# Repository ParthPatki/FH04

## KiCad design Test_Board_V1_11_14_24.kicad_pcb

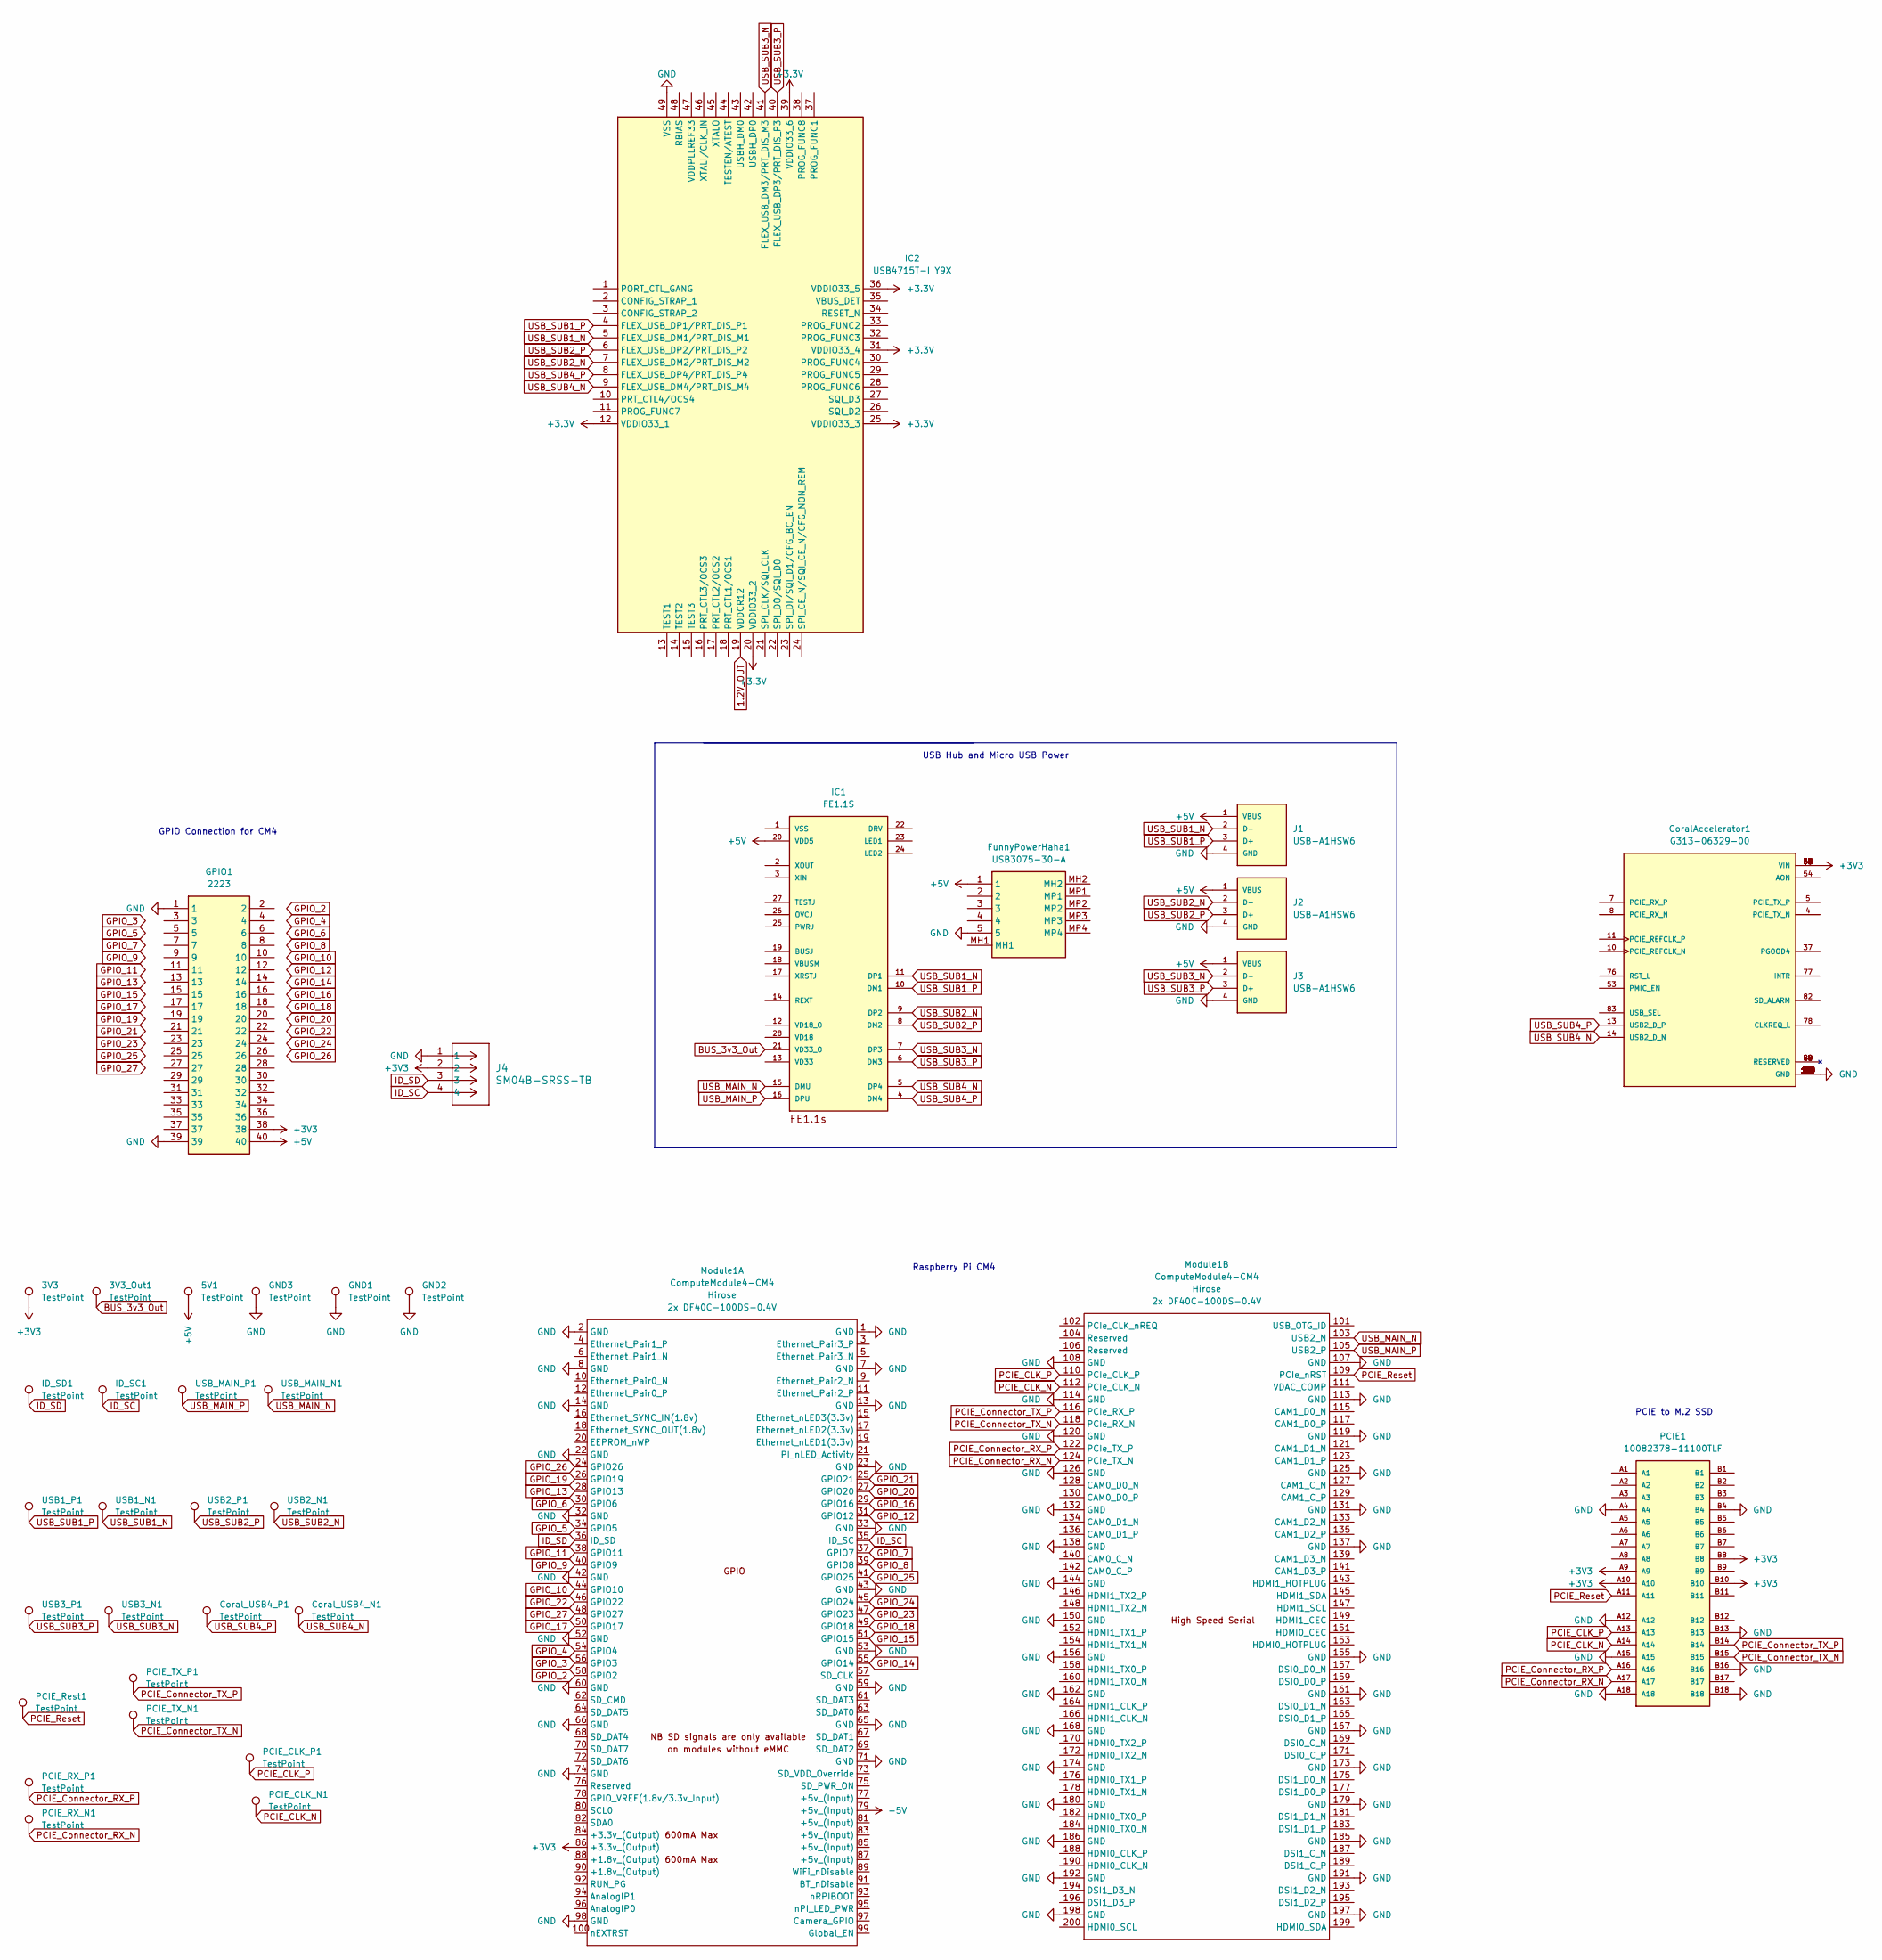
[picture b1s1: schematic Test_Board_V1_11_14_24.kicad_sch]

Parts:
3V3, 3V3_Out1, 5V1: TestPoint; TestPoint_Loop_D1.80mm_Drill1.0mm_Beaded
CoralAccelerator1: G313-06329-00; MODULE_G313-06329-00; PARTREV 1.3
Coral_USB4_N1, Coral_USB4_P1: TestPoint; TestPoint_Loop_D1.80mm_Drill1.0mm_Beaded
FunnyPowerHaha1: USB3075-30-A; USB307530A; Manufacturer_Part_Number USB3075-30-A
GND1, GND2, GND3: TestPoint; TestPoint_Loop_D1.80mm_Drill1.0mm_Beaded
GPIO1: 2223; RHDR40W64P254X254_2X20_5105X500X865P; Manufacturer_Part_Number 2223
IC1: FE1.1S; FE1.1S_SSOP-28
IC2: USB4715T-I_Y9X; QFN50P700X700X100-49N-D; Mouser Part Number 579-USB4715T-I/Y9X
ID_SC1: TestPoint; TestPoint_Loop_D1.80mm_Drill1.0mm_Beaded
ID_SD1: TestPoint; TestPoint_Loop_D1.80mm_Drill1.0mm_Beaded
J1, J2, J3: USB-A1HSW6; OST_USB-A1HSW6; PARTREV A
J4: SM04B-SRSS-TB; CONN_SM04B-SRSS-TB_JST
Module1: ComputeModule4-CM4; Raspberry-Pi-4-Compute-Module
PCIE1: 10082378-11100TLF; AMPHENOL_10018783-11110TLF; PARTREV H
PCIE_CLK_N1: TestPoint; TestPoint_Loop_D1.80mm_Drill1.0mm_Beaded
PCIE_CLK_P1: TestPoint; TestPoint_Loop_D1.80mm_Drill1.0mm_Beaded
PCIE_RX_N1: TestPoint; TestPoint_Loop_D1.80mm_Drill1.0mm_Beaded
PCIE_RX_P1: TestPoint; TestPoint_Loop_D1.80mm_Drill1.0mm_Beaded
PCIE_Rest1: TestPoint; TestPoint_Loop_D1.80mm_Drill1.0mm_Beaded
PCIE_TX_N1: TestPoint; TestPoint_Loop_D1.80mm_Drill1.0mm_Beaded
PCIE_TX_P1: TestPoint; TestPoint_Loop_D1.80mm_Drill1.0mm_Beaded
USB1_N1, USB1_P1, USB2_N1, USB2_P1, USB3_N1, USB3_P1: TestPoint; TestPoint_Loop_D1.80mm_Drill1.0mm_Beaded
USB_MAIN_N1: TestPoint; TestPoint_Loop_D1.80mm_Drill1.0mm_Beaded
USB_MAIN_P1: TestPoint; TestPoint_Loop_D1.80mm_Drill1.0mm_Beaded

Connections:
+3V3: 3V3.1, CoralAccelerator1.56 (VIN), CoralAccelerator1.57 (VIN), CoralAccelerator1.58 (VIN), CoralAccelerator1.59 (VIN), CoralAccelerator1.60 (VIN), CoralAccelerator1.61 (VIN), CoralAccelerator1.62 (VIN), CoralAccelerator1.63 (VIN), CoralAccelerator1.64 (VIN), CoralAccelerator1.65 (VIN), CoralAccelerator1.66 (VIN), CoralAccelerator1.67 (VIN), GPIO1.38, J4.2, Module1.86 (+3.3v_(Output)), PCIE1.A9, PCIE1.A10, PCIE1.B8, PCIE1.B10
+5V: 5V1.1, FunnyPowerHaha1.1, GPIO1.40, IC1.20 (VDD5), J1.1 (VBUS), J2.1 (VBUS), J3.1 (VBUS), Module1.79 (+5v_(Input))
BUS_3v3_Out: 3V3_Out1.1, IC1.21 (VD33_O)
GND: CoralAccelerator1.1 (GND), CoralAccelerator1.2 (GND), CoralAccelerator1.3 (GND), CoralAccelerator1.6 (GND), CoralAccelerator1.9 (GND), CoralAccelerator1.12 (GND), CoralAccelerator1.15 (GND), CoralAccelerator1.16 (GND), CoralAccelerator1.17 (GND), CoralAccelerator1.18 (GND), CoralAccelerator1.19 (GND), CoralAccelerator1.20 (GND), CoralAccelerator1.21 (GND), CoralAccelerator1.22 (GND), CoralAccelerator1.23 (GND), CoralAccelerator1.24 (GND), CoralAccelerator1.25 (GND), CoralAccelerator1.26 (GND), CoralAccelerator1.27 (GND), CoralAccelerator1.28 (GND), CoralAccelerator1.29 (GND), CoralAccelerator1.30 (GND), CoralAccelerator1.31 (GND), CoralAccelerator1.32 (GND), CoralAccelerator1.33 (GND), CoralAccelerator1.34 (GND), CoralAccelerator1.35 (GND), CoralAccelerator1.36 (GND), CoralAccelerator1.38 (GND), CoralAccelerator1.39 (GND), CoralAccelerator1.40 (GND), CoralAccelerator1.41 (GND), CoralAccelerator1.42 (GND), CoralAccelerator1.43 (GND), CoralAccelerator1.44 (GND), CoralAccelerator1.45 (GND), CoralAccelerator1.46 (GND), CoralAccelerator1.47 (GND), CoralAccelerator1.48 (GND), CoralAccelerator1.51 (GND), CoralAccelerator1.55 (GND), CoralAccelerator1.68 (GND), CoralAccelerator1.69 (GND), CoralAccelerator1.70 (GND), CoralAccelerator1.71 (GND), CoralAccelerator1.72 (GND), CoralAccelerator1.73 (GND), CoralAccelerator1.74 (GND), CoralAccelerator1.75 (GND), CoralAccelerator1.79 (GND), CoralAccelerator1.80 (GND), CoralAccelerator1.81 (GND), CoralAccelerator1.86 (GND), CoralAccelerator1.87 (GND), CoralAccelerator1.88 (GND), CoralAccelerator1.89 (GND), CoralAccelerator1.90 (GND), CoralAccelerator1.91 (GND), CoralAccelerator1.92 (GND), CoralAccelerator1.93 (GND), CoralAccelerator1.94 (GND), CoralAccelerator1.95 (GND), CoralAccelerator1.96 (GND), CoralAccelerator1.97 (GND), CoralAccelerator1.98 (GND), CoralAccelerator1.99 (GND), CoralAccelerator1.100 (GND), CoralAccelerator1.101 (GND), CoralAccelerator1.102 (GND), CoralAccelerator1.103 (GND), CoralAccelerator1.104 (GND), CoralAccelerator1.105 (GND), CoralAccelerator1.106 (GND), CoralAccelerator1.107 (GND), CoralAccelerator1.108 (GND), CoralAccelerator1.109 (GND), CoralAccelerator1.110 (GND), CoralAccelerator1.111 (GND), CoralAccelerator1.112 (GND), CoralAccelerator1.113 (GND), CoralAccelerator1.114 (GND), CoralAccelerator1.115 (GND), CoralAccelerator1.116 (GND), CoralAccelerator1.117 (GND), CoralAccelerator1.118 (GND), CoralAccelerator1.119 (GND), CoralAccelerator1.120 (GND), FunnyPowerHaha1.5, GND1.1, GND2.1, GND3.1, GPIO1.1, GPIO1.39, IC2.49 (VSS), J1.4 (GND), J2.4 (GND), J3.4 (GND), J4.1, Module1.1 (GND), Module1.2 (GND), Module1.7 (GND), Module1.8 (GND), Module1.13 (GND), Module1.14 (GND), Module1.22 (GND), Module1.23 (GND), Module1.32 (GND), Module1.33 (GND), Module1.42 (GND), Module1.43 (GND), Module1.52 (GND), Module1.53 (GND), Module1.59 (GND), Module1.60 (GND), Module1.65 (GND), Module1.66 (GND), Module1.71 (GND), Module1.74 (GND), Module1.98 (GND), Module1.107 (GND), Module1.108 (GND), Module1.113 (GND), Module1.114 (GND), Module1.119 (GND), Module1.120 (GND), Module1.125 (GND), Module1.126 (GND), Module1.131 (GND), Module1.132 (GND), Module1.137 (GND), Module1.138 (GND), Module1.144 (GND), Module1.150 (GND), Module1.155 (GND), Module1.156 (GND), Module1.161 (GND), Module1.162 (GND), Module1.167 (GND), Module1.168 (GND), Module1.173 (GND), Module1.174 (GND), Module1.179 (GND), Module1.180 (GND), Module1.185 (GND), Module1.186 (GND), Module1.191 (GND), Module1.192 (GND), Module1.197 (GND), Module1.198 (GND), PCIE1.A4, PCIE1.A12, PCIE1.A15, PCIE1.A18, PCIE1.B4, PCIE1.B13, PCIE1.B16, PCIE1.B18
GPIO_2: Module1.58 (GPIO2)
GPIO_3: Module1.56 (GPIO3)
GPIO_4: Module1.54 (GPIO4)
GPIO_5: Module1.34 (GPIO5)
GPIO_6: Module1.30 (GPIO6)
GPIO_7: Module1.37 (GPIO7)
GPIO_8: Module1.39 (GPIO8)
GPIO_9: Module1.40 (GPIO9)
GPIO_10: Module1.44 (GPIO10)
GPIO_11: Module1.38 (GPIO11)
GPIO_12: Module1.31 (GPIO12)
GPIO_13: Module1.28 (GPIO13)
GPIO_14: Module1.55 (GPIO14)
GPIO_15: Module1.51 (GPIO15)
GPIO_16: Module1.29 (GPIO16)
GPIO_17: Module1.50 (GPIO17)
GPIO_18: Module1.49 (GPIO18)
GPIO_19: Module1.26 (GPIO19)
GPIO_20: Module1.27 (GPIO20)
GPIO_21: Module1.25 (GPIO21)
GPIO_22: Module1.46 (GPIO22)
GPIO_23: Module1.47 (GPIO23)
GPIO_24: Module1.45 (GPIO24)
GPIO_25: Module1.41 (GPIO25)
GPIO_26: Module1.24 (GPIO26)
GPIO_27: Module1.48 (GPIO27)
ID_SC: ID_SC1.1, J4.4, Module1.35 (ID_SC)
ID_SD: ID_SD1.1, J4.3, Module1.36 (ID_SD)
unnamed: IC2.12 (VDDIO33_1), IC2.20 (VDDIO33_2), IC2.25 (VDDIO33_3), IC2.31 (VDDIO33_4), IC2.36 (VDDIO33_5), IC2.39 (VDDIO33_6)
PCIE_CLK_N: Module1.112 (PCIe_CLK_N), PCIE1.A14, PCIE_CLK_N1.1
PCIE_CLK_P: Module1.110 (PCIe_CLK_P), PCIE1.A13, PCIE_CLK_P1.1
PCIE_Connector_RX_N: Module1.124 (PCIe_TX_N), PCIE1.A17, PCIE_RX_N1.1
PCIE_Connector_RX_P: Module1.122 (PCIe_TX_P), PCIE1.A16, PCIE_RX_P1.1
PCIE_Connector_TX_N: Module1.118 (PCIe_RX_N), PCIE1.B15, PCIE_TX_N1.1
PCIE_Connector_TX_P: Module1.116 (PCIe_RX_P), PCIE1.B14, PCIE_TX_P1.1
PCIE_Reset: Module1.109 (PCIe_nRST), PCIE1.A11, PCIE_Rest1.1
USB_MAIN_N: IC1.15 (DMU), Module1.103 (USB2_N), USB_MAIN_N1.1
USB_MAIN_P: IC1.16 (DPU), Module1.105 (USB2_P), USB_MAIN_P1.1
USB_SUB1_N: IC1.11 (DP1), IC2.5 (FLEX_USB_DM1/PRT_DIS_M1), J1.2 (D-), USB1_N1.1
USB_SUB1_P: IC1.10 (DM1), IC2.4 (FLEX_USB_DP1/PRT_DIS_P1), J1.3 (D+), USB1_P1.1
USB_SUB2_N: IC1.9 (DP2), IC2.7 (FLEX_USB_DM2/PRT_DIS_M2), J2.2 (D-), USB2_N1.1
USB_SUB2_P: IC1.8 (DM2), IC2.6 (FLEX_USB_DP2/PRT_DIS_P2), J2.3 (D+), USB2_P1.1
USB_SUB3_N: IC1.7 (DP3), IC2.41 (FLEX_USB_DM3/PRT_DIS_M3), J3.2 (D-), USB3_N1.1
USB_SUB3_P: IC1.6 (DM3), IC2.40 (FLEX_USB_DP3/PRT_DIS_P3), J3.3 (D+), USB3_P1.1
USB_SUB4_N: CoralAccelerator1.14 (USB2_D_N), Coral_USB4_N1.1, IC1.5 (DP4), IC2.9 (FLEX_USB_DM4/PRT_DIS_M4)
USB_SUB4_P: CoralAccelerator1.13 (USB2_D_P), Coral_USB4_P1.1, IC1.4 (DM4), IC2.8 (FLEX_USB_DP4/PRT_DIS_P4)

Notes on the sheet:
USB Hub and Micro USB Power
PCIE to M.2 SSD
GPIO Connection for CM4
Raspberry Pi CM4

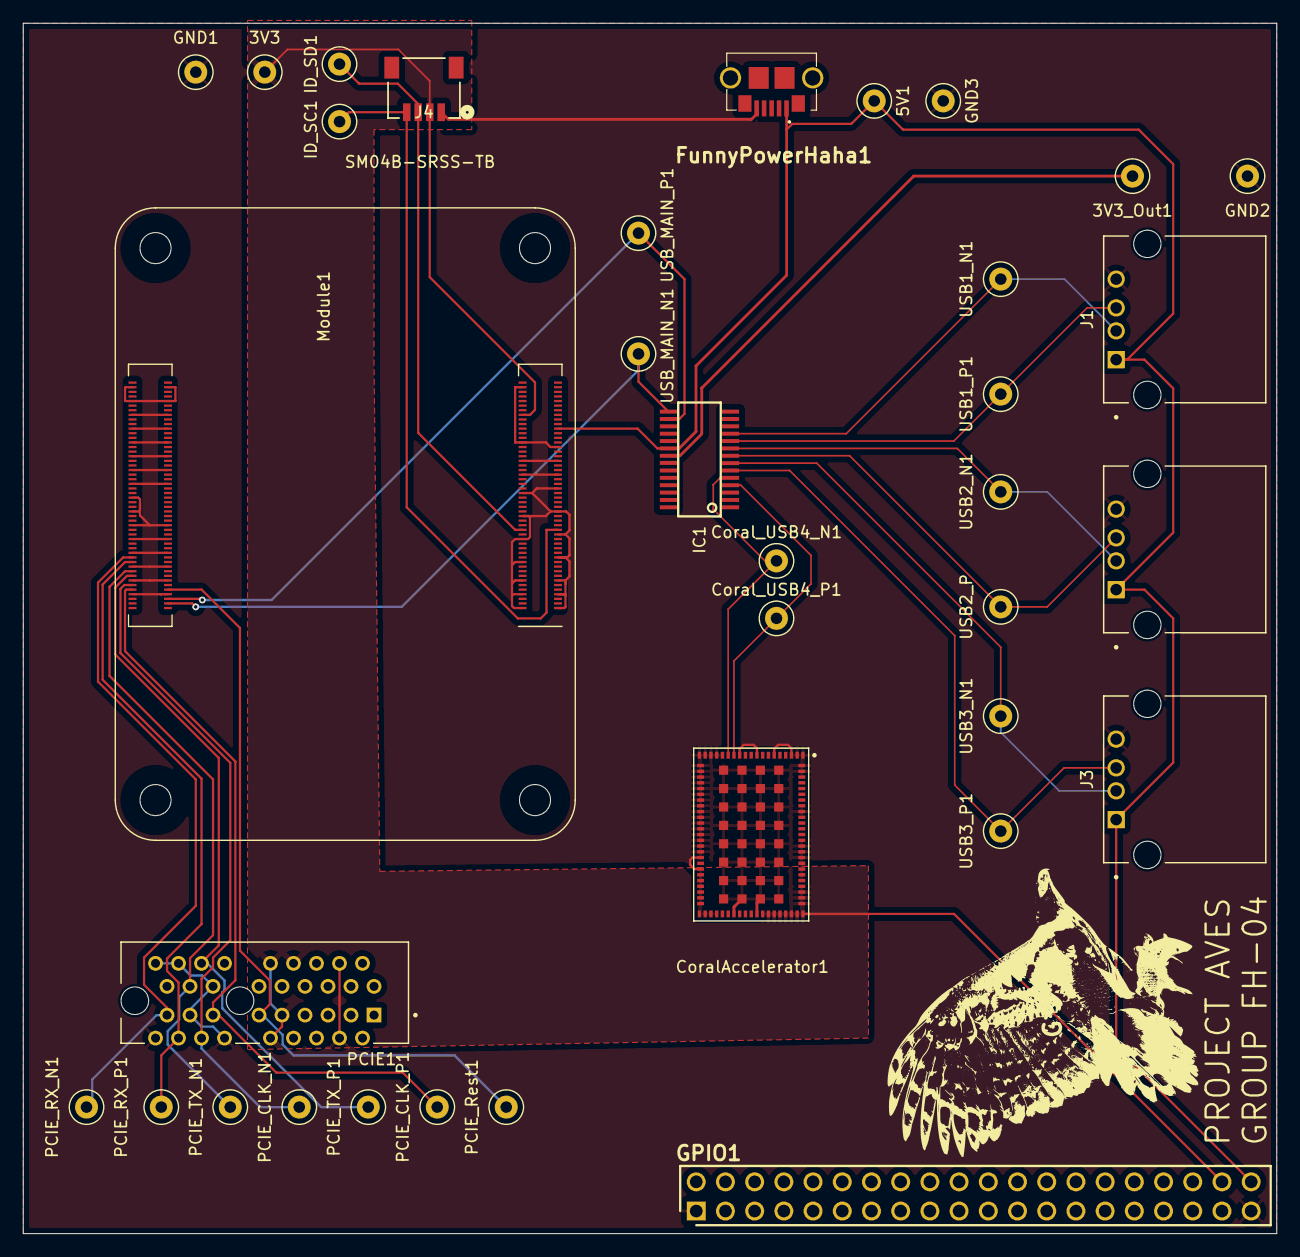
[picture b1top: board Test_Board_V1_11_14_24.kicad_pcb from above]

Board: 2 copper layers, 109.0 x 105.2 mm, 35 parts (0 on the bottom side), 23 nets.

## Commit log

2024-11-21 footprints added and spaced
2024-11-22 All traces done except GPIO
2024-11-24 more traces done
2024-12-10 pcie connector fixed
